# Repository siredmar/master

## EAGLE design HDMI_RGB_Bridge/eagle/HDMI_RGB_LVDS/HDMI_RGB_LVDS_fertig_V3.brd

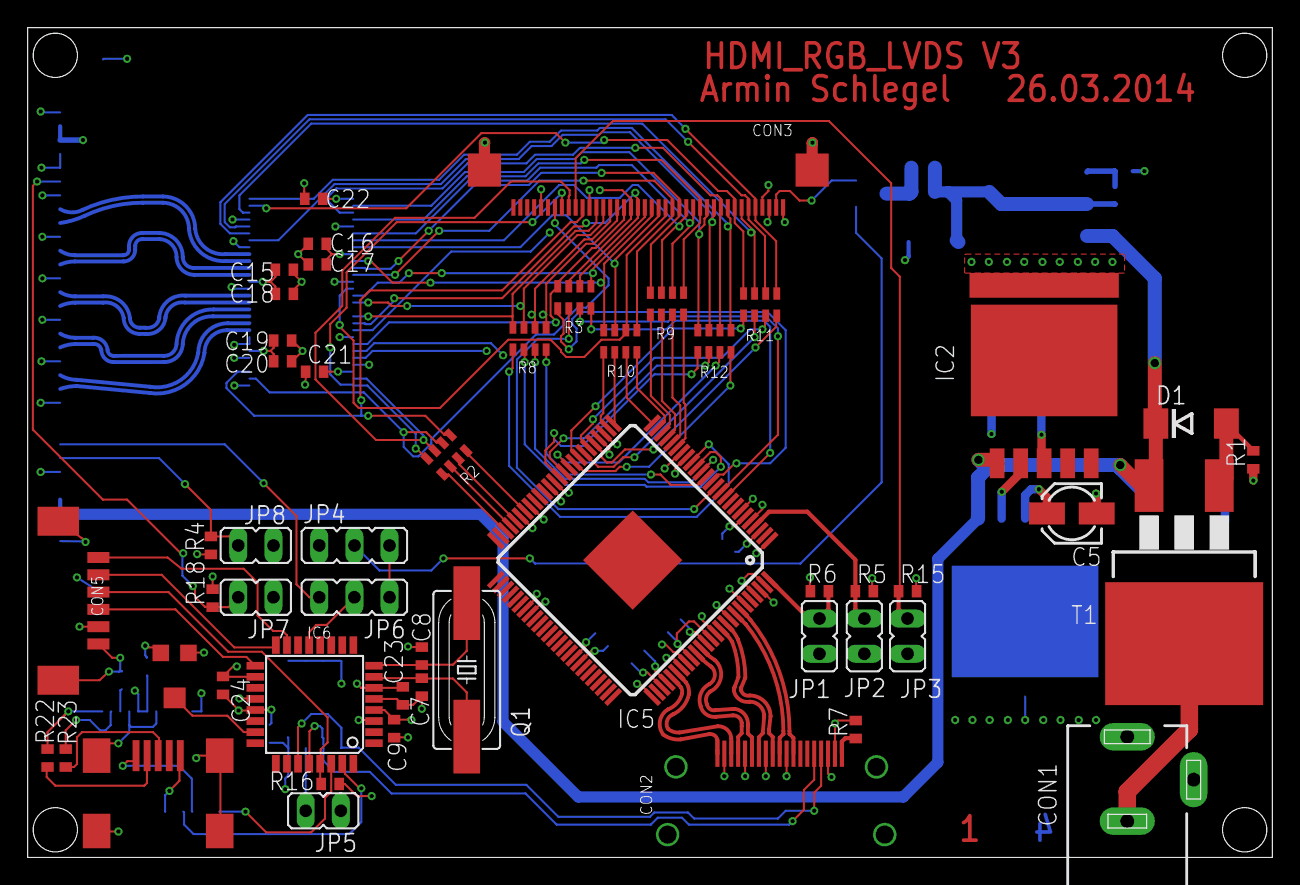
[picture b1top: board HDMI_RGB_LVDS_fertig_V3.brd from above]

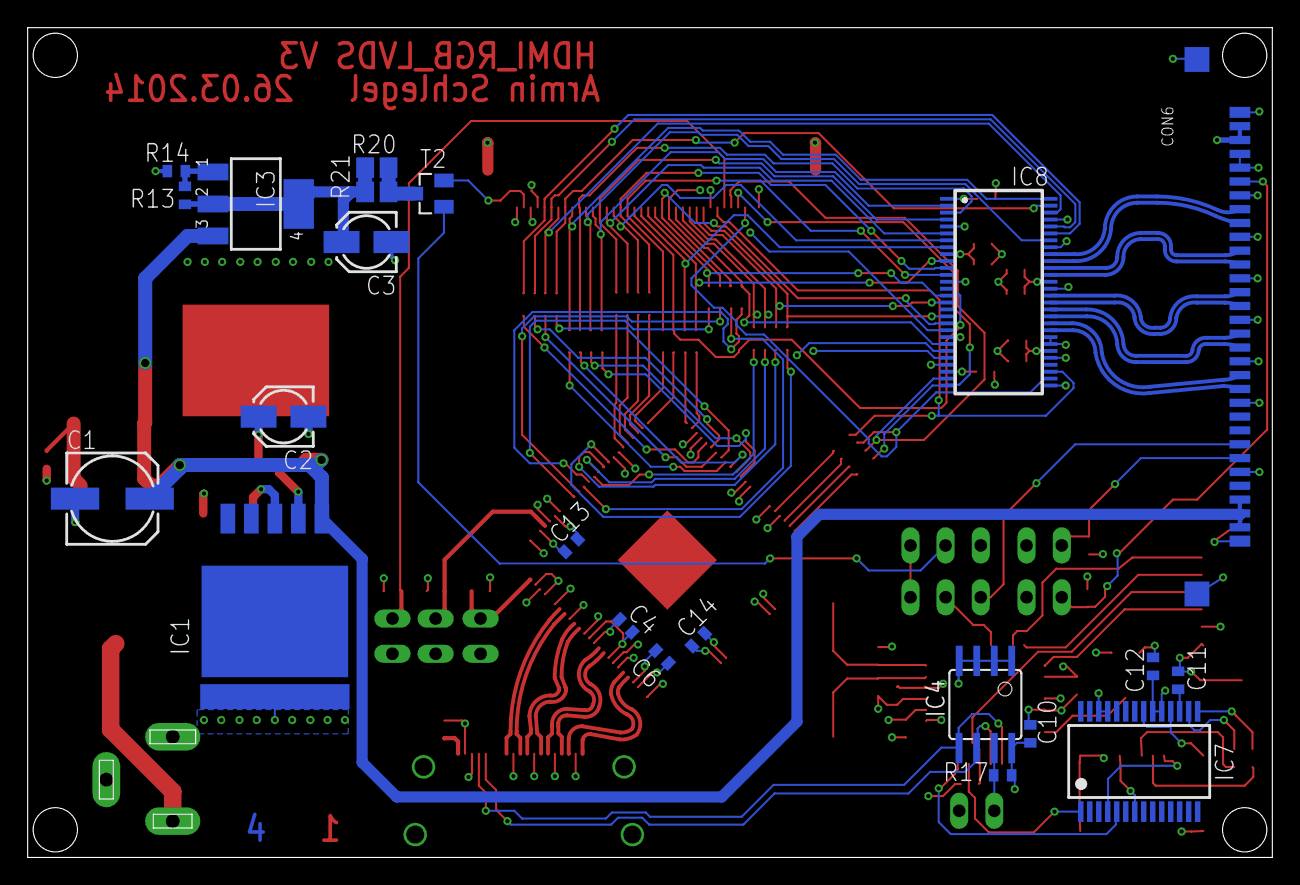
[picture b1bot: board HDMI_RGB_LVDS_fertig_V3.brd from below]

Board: 4 copper layers, 90.0 x 60.0 mm, 79 parts (22 on the bottom side), 111 nets.

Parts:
C1: 100u; C_POL_6X6MM
C2, C3, C5: 10u; C_POL_4X4MM
C4, C6, C9, C10, C11, C12, C13, C14, C23, C24: 100n; C0402
C7, C8: 10p; C0402
C15, C17, C19, C21, C22: 0.01u; C0402
C16, C18, C20: 0.1u; C0402
CON1: KLDX-0202-A-LT
CON2: FCI-10029449-111RLF
CON3: XF2M-4015-1A
CON4: FCI-10033526-N3212LF
CON5: MOLEX-53261-0671
CON6: FI-X30SSLA-HF
D1: BZG03C15TR3; DO214A
IC1: WPMDL1300501BD; TO263-5
IC2: WPMDL1300331BD; TO263-5
IC3: TLV1117CDCYR; SOT223
IC4: AT24C01C-SSHM-B; SOIC8
IC5: TFP401APZP; HTQFP-100
IC6: ATMEGA48A-AU; TQFP32
IC7: FT232RL; SSOP28
IC8: SN75LVDS83BDGGR; TSSOP-56
JP1, JP2, JP3: JUMPER2; JUMPER2_THROUGHHOLE
JP4, JP6: JUMPER3; JUMPER3_THROUGHHOLE
JP5, JP7, JP8: JUMPER2_THROUGHHOLE
Q1: ATS073ASM-1; HC49/USSM
R1: 100k; R0402
R2, R3, R8, R9, R10, R11, R12: 22R; R-ARRAY-4X0603
R4, R5, R6, R15, R16, R17, R18: 10k; R0402
R7: 100R; R0402
R13: 4k7; R0402
R14: 31k4; R0402
R19: 10k; 35WR5KLFTR
R20, R21: 140R; R2512
R22, R23: 0R; R0402
T1: IRF9530NSTRRPBF; D2PAK
T2: IRLML2502TRPBF; SOT23
U$1, U$2, U$3, U$4, U$5, U$15: FRAME_A3_LANDSCAPE; FRAME

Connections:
+3V3: C2.+, C4.2, C6.2, C13.2, C14.2, C15.2, C16.2, C17.2, C18.2, C19.2, C20.2, C21.2, C22.2, CON3.4, CON6.1, CON6.2, IC2.3, IC5.6, IC5.18, IC5.29, IC5.38, IC5.43, IC5.57, IC5.67, IC5.78, IC5.82, IC5.84, IC5.88, IC5.95, IC5.97, IC5.99, IC8.1, IC8.9, IC8.26, IC8.34, IC8.44, JP4.1, R4.2, R5.2, R6.2, R15.2, R18.2
+5V: C5.+, C9.1, C10.2, C12.1, C23.1, C24.1, CON2.18, CON4.1, CON5.5, IC1.3, IC4.8, IC6.4, IC6.6, IC6.18, IC6.20, IC7.4, IC7.19, IC7.20, R7.2, R16.1, R17.2, R19.1
+9V6: C3.+, IC3.2, IC3.4, R13.2, R20.2, R21.2
+12V: C1.+, CON6.28, CON6.29, CON6.30, D1.C, IC1.1, IC2.1, IC3.3, T1.3
AVR_!RESET: CON5.3, IC6.29, R16.2
AVR_MISO: CON5.2, IC6.16
AVR_MOSI: CON5.1, IC6.15
AVR_PWM: IC6.13, JP6.2
AVR_PWM_ADC: IC6.23, R19.2
AVR_SCK: CON5.4, IC6.17
AVR_XTAL1: C7.2, IC6.7, Q1.2
AVR_XTAL2: C8.2, IC6.8, Q1.1
EDID_SCL: CON2.15, IC4.6, IC6.28
EDID_SDA: CON2.16, IC4.5, IC6.27
EDID_WP: IC4.7, JP5.2, R17.1
FTDI_3V3OUT: C11.1, IC7.17
FTDI_RXD: IC6.31, IC7.5
FTDI_TXD: IC6.30, IC7.1
GND: C1.-, C2.-, C3.-, C4.1, C5.-, C6.1, C7.1, C8.1, C9.2, C10.1, C11.2, C12.2, C13.1, C14.1, C15.1, C16.1, C17.1, C18.1, C19.1, C20.1, C21.1, C22.1, C23.2, C24.2, CON1.1, CON1.2, CON2.2, CON2.5, CON2.8, CON2.11, CON2.17, CON2.GND@1, CON2.GND@2, CON2.GND@3, CON2.GND@4, CON3.1, CON3.3, CON3.29, CON3.36, CON3.GND@1, CON3.GND@2, CON4.5, CON4.GND@1, CON4.GND@2, CON4.GND@3, CON4.GND@4, CON5.6, CON5.GND@1, CON5.GND@2, CON6.3, CON6.4, CON6.6, CON6.9, CON6.12, CON6.15, CON6.18, CON6.21, CON6.26, CON6.GND@1, CON6.GND@2, CON6.GND@3, CON6.GND@4, IC1.2, IC1.6, IC2.2, IC2.6, IC4.1, IC4.2, IC4.3, IC4.4, IC5.1, IC5.3, IC5.5, IC5.7, IC5.19, IC5.28, IC5.39, IC5.45, IC5.58, IC5.68, IC5.76, IC5.79, IC5.83, IC5.87, IC5.89, IC5.92, IC5.98, IC6.3, IC6.5, IC6.21, IC7.7, IC7.18, IC7.21, IC7.25, IC7.26, IC8.5, IC8.13, IC8.21, IC8.25, IC8.29, IC8.33, IC8.35, IC8.36, IC8.43, IC8.49, IC8.53, JP1.1, JP2.1, JP3.1, JP5.1, JP7.1, JP8.1, R1.1, R14.2, R19.3
HDMI_CLK_N: CON2.12, IC5.94
HDMI_CLK_P: CON2.10, IC5.93
HDMI_DAT0_N: CON2.9, IC5.91
HDMI_DAT0_P: CON2.7, IC5.90
HDMI_DAT1_N: CON2.6, IC5.86
HDMI_DAT1_P: CON2.4, IC5.85
HDMI_DAT2_N: CON2.3, IC5.81
HDMI_DAT2_P: CON2.1, IC5.80
HDMI_OCK_INV: IC5.100, JP1.2, R6.1
HDMI_PIXS: IC5.4, JP2.2, R5.1
LVDS_0_N: CON6.7, IC8.48
LVDS_0_P: CON6.8, IC8.47
LVDS_1_N: CON6.10, IC8.46
LVDS_1_P: CON6.11, IC8.45
LVDS_2_N: CON6.13, IC8.42
LVDS_2_P: CON6.14, IC8.41
LVDS_3_N: CON6.19, IC8.38
LVDS_3_P: CON6.20, IC8.37
LVDS_CLK_N: CON6.16, IC8.40
LVDS_CLK_P: CON6.17, IC8.39
LVDS_LED_EN: CON6.25, JP8.2, R4.1
LVDS_PWM: CON6.24, JP6.3
LVDS_REVSCAN: CON6.5, JP7.2, R18.1
unnamed: IC5.48, R2.1M
unnamed: CON1.3, T1.2
unnamed: D1.A, R1.2, T1.1
unnamed: IC7.15, R22.2
unnamed: IC5.47, R2.2M
unnamed: IC5.46, R2.3M
unnamed: IC5.44, R2.4M
unnamed: IC5.13, R3.1M
unnamed: IC7.16, R23.2
unnamed: IC5.12, R3.2M
unnamed: IC5.11, R3.3M
unnamed: IC5.10, R3.4M
unnamed: IC5.17, R8.1M
unnamed: IC5.16, R8.2M
unnamed: IC5.15, R8.3M
unnamed: IC5.14, R8.4M
unnamed: CON2.19, R7.1
unnamed: IC5.23, R9.1M
unnamed: IC5.22, R9.2M
unnamed: IC5.21, R9.3M
unnamed: IC5.20, R9.4M
unnamed: IC5.27, R10.1M
unnamed: IC5.26, R10.2M
unnamed: IC5.25, R10.3M
unnamed: IC5.24, R10.4M
unnamed: IC5.33, R11.1M
unnamed: IC5.32, R11.2M
unnamed: IC5.31, R11.3M
unnamed: IC5.30, R11.4M
unnamed: IC5.37, R12.1M
unnamed: IC5.36, R12.2M
unnamed: IC5.35, R12.3M
unnamed: IC5.34, R12.4M
unnamed: IC3.1, R13.1, R14.1
unnamed: CON3.2, T2.2
unnamed: R20.1, R21.1, T2.3
RGB_DE: CON3.34, IC8.30, R2.3P
RGB_DISP: CON3.31, JP3.2, R15.1
RGB_EVEN_B0: CON3.21, IC8.15, R3.4P
RGB_EVEN_B1: CON3.22, IC8.19, R3.3P
RGB_EVEN_B2: CON3.23, IC8.20, R3.2P
RGB_EVEN_B3: CON3.24, IC8.22, R3.1P
RGB_EVEN_B4: CON3.25, IC8.23, R8.4P
RGB_EVEN_B5: CON3.26, IC8.24, R8.3P
RGB_EVEN_B6: CON3.27, IC8.16, R8.2P
RGB_EVEN_B7: CON3.28, IC8.18, R8.1P
RGB_EVEN_G0: CON3.13, IC8.4, R9.4P
RGB_EVEN_G1: CON3.14, IC8.6, R9.3P
RGB_EVEN_G2: CON3.15, IC8.7, R9.2P
RGB_EVEN_G3: CON3.16, IC8.11, R9.1P
RGB_EVEN_G4: CON3.17, IC8.12, R10.4P
RGB_EVEN_G5: CON3.18, IC8.14, R10.3P
RGB_EVEN_G6: CON3.19, IC8.8, R10.2P
RGB_EVEN_G7: CON3.20, IC8.10, R10.1P
RGB_EVEN_R0: CON3.5, IC8.51, R11.4P
RGB_EVEN_R1: CON3.6, IC8.52, R11.3P
RGB_EVEN_R2: CON3.7, IC8.54, R11.2P
RGB_EVEN_R3: CON3.8, IC8.55, R11.1P
RGB_EVEN_R4: CON3.9, IC8.56, R12.4P
RGB_EVEN_R5: CON3.10, IC8.3, R12.3P
RGB_EVEN_R6: CON3.11, IC8.50, R12.2P
RGB_EVEN_R7: CON3.12, IC8.2, R12.1P
RGB_HSYNC: CON3.32, IC8.27, R2.2P
RGB_ODCK: CON3.30, IC8.31, R2.4P
RGB_PWM: JP4.3, JP6.1
RGB_PWM_EN: JP4.2, T2.1
RGB_VSYNC: CON3.33, IC8.28, R2.1P
USB_D+: CON4.3, R23.1
USB_D-: CON4.2, R22.1

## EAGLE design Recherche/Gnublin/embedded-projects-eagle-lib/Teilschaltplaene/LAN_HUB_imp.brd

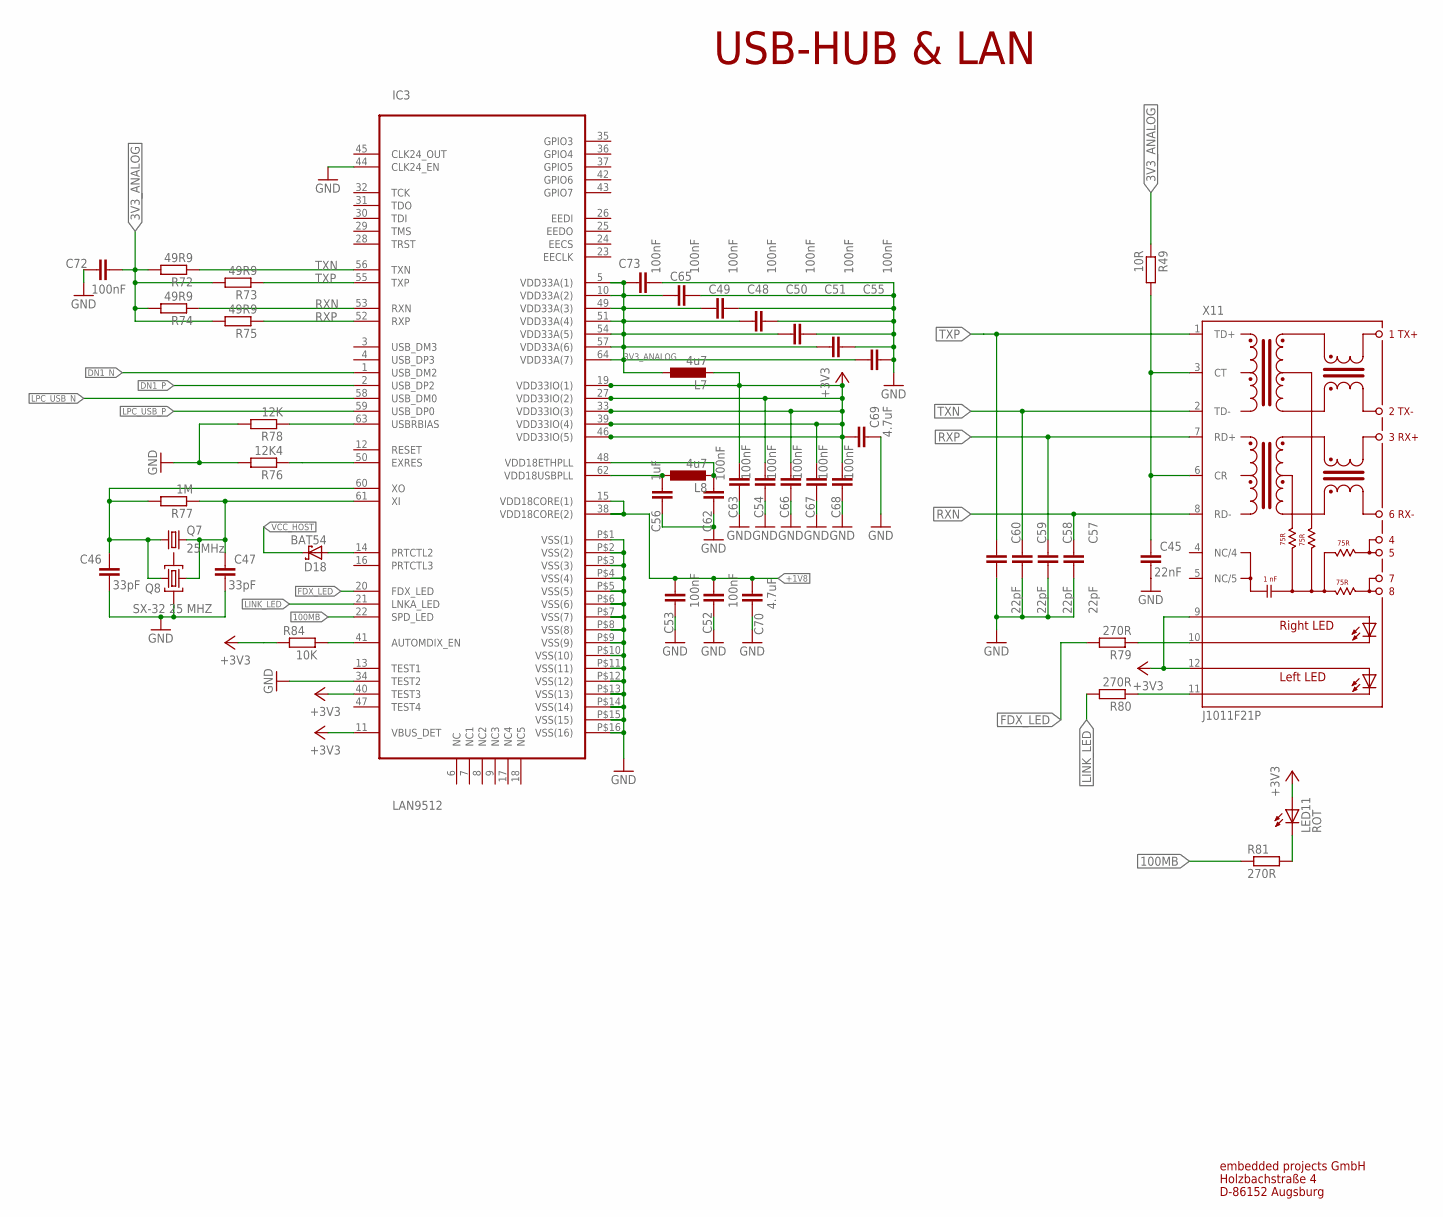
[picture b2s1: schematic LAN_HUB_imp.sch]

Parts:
C45: 22nF; C0805
C46, C47: 33pF; C0805
C48, C49, C50, C51, C52, C53, C54, C55, C62, C63, C65, C66, C67, C68, C72, C73: 100nF; C0805
C56: 1uF; C0805
C57, C58, C59, C60: 22pF; C0805
C69, C70: 4.7uF; C0805
D18: BAT54; SOT-23
IC3: LAN9512; QFN-64; FARNELL 2292586
L7, L8: 4u7; PSU3014
LED11: ROT; LED_CHIP-LED0805
Q7: 25MHz; HC49UP
Q8: SX-32 25 MHZ; SX-32; FARNELL 1712841
R49: 10R; R0805
R72, R73, R74, R75: 49R9; R0805
R76: 12K4; R0805
R77: 1M; R0805
R78: 12K; R0805
R79, R80, R81: 270R; R0805
R84: 10K; R0805
X11: J1011F21P; J1

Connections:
3V3_ANALOG: C48.2, C49.2, C50.2, C51.2, C55.2, C65.2, C72.1, C73.2, IC3.5 (VDD33A(1)), IC3.10 (VDD33A(2)), IC3.49 (VDD33A(3)), IC3.51 (VDD33A(4)), IC3.54 (VDD33A(5)), IC3.57 (VDD33A(6)), IC3.64 (VDD33A(7)), L7.2, R49.1, R72.2, R73.2, R74.2, R75.2
100MB: IC3.22 (SPD_LED), R81.1
+1V8: C52.2, C53.2, C70.1, IC3.15 (VDD18CORE(1)), IC3.38 (VDD18CORE(2))
+3V3: C54.2, C63.2, C66.2, C67.2, C68.2, C69.2, IC3.11 (VBUS_DET), IC3.19 (VDD33IO(1)), IC3.27 (VDD33IO(2)), IC3.33 (VDD33IO(3)), IC3.39 (VDD33IO(4)), IC3.40 (TEST3), IC3.46 (VDD33IO(5)), L7.1, LED11.A, R84.1, X11.9 (A-R), X11.12 (AL)
DN1_N: IC3.1 (USB_DM2)
DN1_P: IC3.2 (USB_DP2)
FDX_LED: IC3.20 (FDX_LED), R79.2
GND: C45.1, C46.1, C47.1, C48.1, C49.1, C50.1, C51.1, C52.1, C53.1, C54.1, C55.1, C56.2, C57.1, C58.1, C59.1, C60.1, C62.2, C63.1, C65.1, C66.1, C67.1, C68.1, C69.1, C70.2, C72.2, C73.1, IC3.34 (TEST2), IC3.44 (CLK24_EN), IC3.P$1 (VSS(1)), IC3.P$2 (VSS(2)), IC3.P$3 (VSS(3)), IC3.P$4 (VSS(4)), IC3.P$5 (VSS(5)), IC3.P$6 (VSS(6)), IC3.P$7 (VSS(7)), IC3.P$8 (VSS(8)), IC3.P$9 (VSS(9)), IC3.P$10 (VSS(10)), IC3.P$11 (VSS(11)), IC3.P$12 (VSS(12)), IC3.P$13 (VSS(13)), IC3.P$14 (VSS(14)), IC3.P$15 (VSS(15)), IC3.P$16 (VSS(16)), Q8.2 (3), R76.2, R78.2
LINK_LED: IC3.21 (LNKA_LED), R80.2
LPC_USB_N: IC3.58 (USB_DM0)
LPC_USB_P: IC3.59 (USB_DP0)
unnamed: C56.1, IC3.62 (VDD18USBPLL), L8.2
unnamed: LED11.C, R81.2
unnamed: C45.2, R49.2, X11.3 (CT), X11.6 (CR)
unnamed: IC3.50 (EXRES), R76.1
unnamed: C62.1, IC3.48 (VDD18ETHPLL), L8.1
unnamed: C46.2, IC3.60 (XO), Q7.1, Q8.3 (2), R77.2
unnamed: C47.2, IC3.61 (XI), Q7.2, Q8.1, R77.1
unnamed: IC3.63 (USBRBIAS), R78.1
unnamed: R79.1, X11.10 (C-R)
unnamed: R80.1, X11.11 (C-L)
unnamed: IC3.41 (AUTOMDIX_EN), R84.2
unnamed: D18.1 (A), IC3.14 (PRTCTL2)
RXN: C57.2, IC3.53 (RXN), R74.1, X11.8 (RD-)
RXP: C58.2, IC3.52 (RXP), R75.1, X11.7 (RD+)
TXN: C59.2, IC3.56 (TXN), R72.1, X11.2 (TD-)
TXP: C60.2, IC3.55 (TXP), R73.1, X11.1 (TD+)
VCC_HOST: D18.3 (C)

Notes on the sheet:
USB-HUB & LAN
embedded projects GmbH
Holzbachstraße 4
D-86152 Augsburg

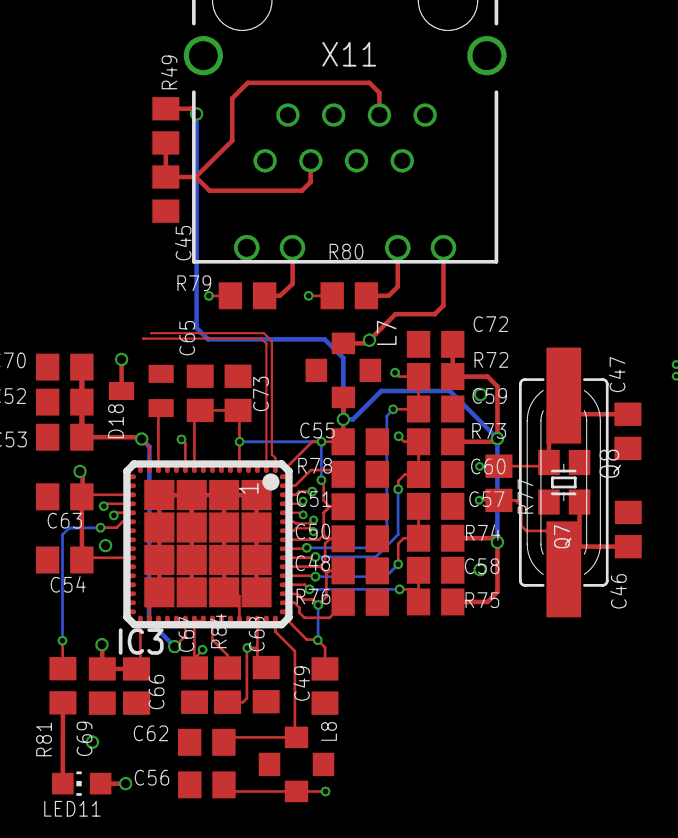
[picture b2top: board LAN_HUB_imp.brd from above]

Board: 4 copper layers, 46 parts (0 on the bottom side), 23 nets.
